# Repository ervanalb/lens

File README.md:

# lens
*lens* stands for "live editing of network streams"

*lens* is a framework that allows you to tap live cabling for inspection and injection.

Defcon 23
=========

Watch the video of our presentation [here](https://www.youtube.com/watch?v=RoOqznZUClI)!

[Slides](docs/LENS_DEFCON_23_slides.pdf) & [whitepaper](docs/lens_whitepaper.pdf) are available in the [docs/](docs) folder.

Or, photos of the device we presented can be found [here](http://eric.van.al/lens).

You can reach us through github, or our emails are listed in our github profiles ([Zach](https://github.com/zbanks/), [Eric](https://github.com/ervanalb/)).

Hardware
========

The wires of a network cable can be punched down into the *lens* tap board in two places without interrupting the packet flow. The tap board then provides a redundant copper path through a set of relays. Once all of the wires have been punched down on both sides, they can be cut so that the signals are now routed only through the relays on the tap board.

One or two additional NICs are connected to the tap board on its TAP ports. These, along with a USB link, are connected to a computer. The computer can command the relays over USB to assume either a passive or active tap topology, or a transparent pass-through mode.

The tap board has three safety features: fail-safe power loss, heartbeat, and tamper detection. If the board detects that power has been lost, it can optionally use the remaining energy stored in a large capacitor to revert the state of the relays to pass-through mode. Alternatively, if the board fails to receive a heartbeat from the computer within a specified amount of time, such as if the computer software crashes, it can revert the relays. Lastly, the board has an accelerometer on it that can detect if the board is jostled or moved and report that to the computer. This can give you peace of mind that your board is still in-place and working.

Software
========

The *lens* software was made to work nicely with the tap board, but can be used without it. Simply connect two NICs in a man-in-the-middle configuration.

*lens* implements a software network stack designed for man-in-the-middle attacks. It is able to decode many protocols, edit their data payloads, and forge new packets containing the modified payloads that look as similar to the original ones as possible.

*lens* is single-threaded and uses asynchronous I/O through *tornado*. Many operations are implemented as tornado coroutines.

Network Layers
--------------

The software is split into *layers*, each of which manages its own state and provides an abstraction for the layers above it. These layers generally follow the standard "OSI Model." For instance, *Ethernet*, *IPv4*, *TCP*, *HTTP*, are some of the layers we have.

### State & Connections

Some layers are inherently stateful with respect to the data that is passed through them (e.g. TCP), whereas others do not require any state to handle their data (e.g. IPv4). However, these layers may find it useful to maintain state in order to later forge packets.

Layers are represented as subclasses of ``NetLayer``. Layers are chained together to form a doubly-linked DAG (typically a tree), where each layer knows its *parent* (``parent``) and its *children* (``children``) that come "above" it in the stack. For example, an instance of ``EthernetLayer`` may have an ``IPv4Layer`` in its ``children`` list. That ``IPv4Layer``'s ``parent`` would be a reference back to the ``EthernetLayer`` instance.

For the purposes of this document, this kind of relationship will be described as ``EthernetLayer --> IPv4Layer``, even though the connection is in fact double-ended, and the layers are instances.

### Methods

Each layer (subclassing ``NetLayer``) should implement the following methods as tornado coroutines:

- ``Layer.on_read(self, src, header, payload)``

This coroutine is called whenever there is new data (``payload``) available for the layer to process. ``header`` is a ``dict`` which holds all of the information extracted from all of the previous layers. With ``payload`` and ``header``, it should be possible to completely reconstruct the original packet. ``src`` represents where the data came from. A simple ``on_read`` might move some data from ``payload`` into ``header`` and call ``Layer.bubble(src, new_header, sub_payload)`` to pass data to children layers.

- ``Layer.write(self, dst, header, payload)``

This coroutine is called to write out ``payload``. A simple ``write`` would take relevant parameters in ``header``, re-serialize them, and combine them with ``payload`` to form a new payload. It would then call ``Layer.write_back(dst, header, new_payload)`` to pass the back to the parent layer.

- ``Layer.match(self, src, header)``

This function should return a boolean indicating whether this layer is capable of handling the given packet. The default behavior, if not overridden, is to always return ``True``, that is, consume all data.

#### Routing

Currently, ``src`` and ``dst`` parameters represent which physical NIC the message came from or is intended to go to. ``NetLayer`` implements two functions, ``route(src)`` and ``unroute(dst)``, which are intended to resolve the intended recipient of a packet. This mechanism might need to be re-worked for systems with 3+ NICs. Currently, the two NICs are represented by ``0`` and ``1``, so the functions are equivalent.

#### Useful Methods

Although each ``NetLayer`` should implement the methods above, there are some additional helper methods/coroutines that are useful:

- ``Layer.bubble(self, src, header, payload)``

This coroutine will attempt to further decode a payload using this layer's ``children``. It will go through the list of children until it finds one whose ``match(...)`` function returns ``True``. It will then call that child's ``on_read(...)`` function. If no child matches, it calls ``self.write(dst, ...)``, resolving ``dst`` from ``src``, at which point the program flow "reverses direction".

This method is used to pass data on to higher layers for further decoding. If no higher layer is available or connected it will re-write (loopback) the data unchanged.

- ``Layer.write_back(self, dst, header, payload)`` 

This coroutine calls ``self.parent.write(dst, header, payload)``. It is for further encoding a payload using this layer's ``parent``. It can be thought of as the opposite of ``Layer.bubble(...)``.

- ``Layer.passthru(self, src, header, payload)``

This convenience coroutine will call ``self.write_back(dst, ...)`` with ``dst`` resolved from ``src``.

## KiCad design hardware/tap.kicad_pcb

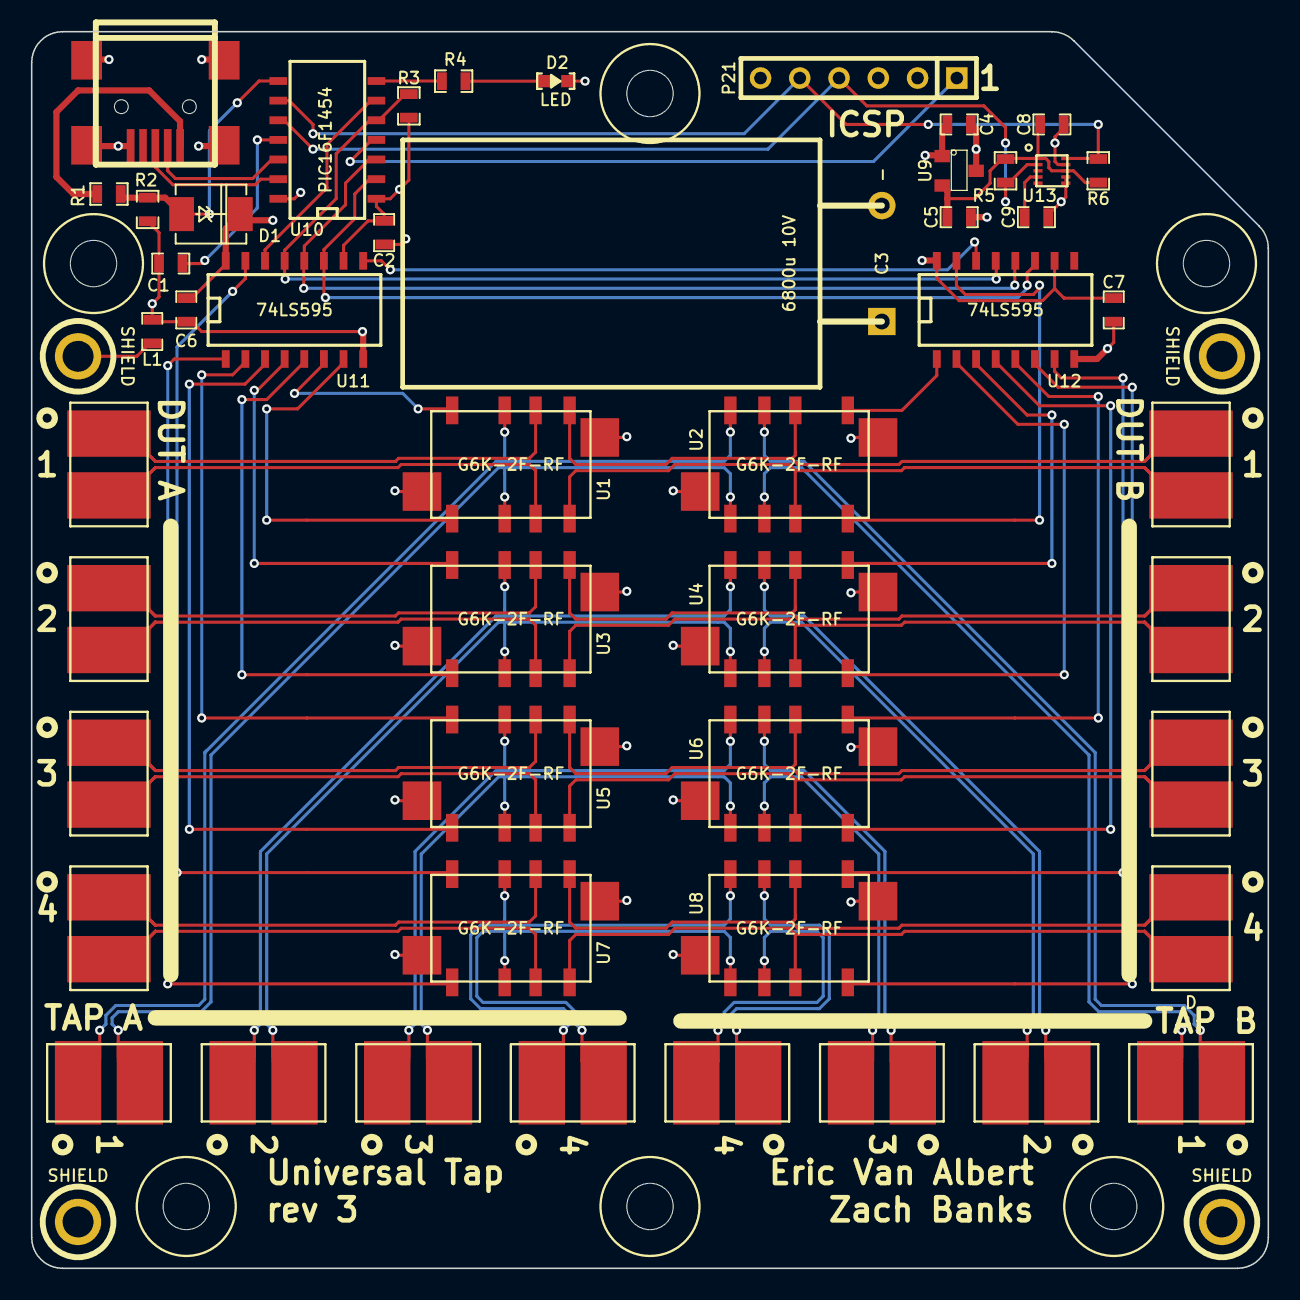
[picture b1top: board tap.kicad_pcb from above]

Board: 4 copper layers, 80.0 x 80.0 mm, 59 parts (0 on the bottom side), 68 nets.

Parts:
C1: 470nF; SM0603_Capa
C2, C6, C7, C8, C9: 100n; SM0603_Capa
C3: 6800u 10V; C2V10
C4, C5: 1u; SM0603_Capa
CON1: USB-MINI-B; USB_MINI_B
D1: DIODE; DO-214AC(SMA)
D2: LED; LED-0603
HOLE: VAL**; HOLE
HOLE#2, HOLE#3, HOLE#4, HOLE#5, HOLE#6: VAL**; HOLE
L1: FERRITE; SM0603_Capa
P1, P6, P11, P16: H; 00-9176-002
P2, P7, P12, P17: HTAP; 00-9176-002
P3, P8, P22, P23: CONN_1; 1pin
P4, P9, P14, P19: DTAP; 00-9176-002
P5, P10, P15, P20: D; 00-9176-002
P21: ICSP; SIL-6
R1: 22R; SM0603_Resistor
R2, R3: 10K; SM0603_Resistor
R4: 100R; SM0603_Resistor
R5, R6: 4K7; SM0603_Resistor
U1, U2, U3, U4, U5, U6, U7, U8: G6K-2F-RF
U9: 3v3; SOT23
U10: PIC16F1454; SO14N
U11, U12: 74LS595; SO16N
U13: MMA8653FC; DFN_10

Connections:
3V3: C5.1, C8.1, R5.1, R6.1, U9.2, U13.1, U13.8
/1/DC+: U2.1, U12.1
/1/DC-: U2.8, U12.15
/1/HC+: U1.1, U11.7
/1/HC-: U1.8, U11.6
/2/DC+: U4.1, U12.3
/2/DC-: U4.8, U12.2
/2/HC+: U3.1, U11.5
/2/HC-: U3.8, U11.4
/3/DC+: U6.1, U12.5
/3/DC-: U6.8, U12.4
/3/HC+: U5.1, U11.3
/3/HC-: U5.8, U11.2
/4/DC+: U8.1, U12.7
/4/DC-: U8.8, U12.6
/4/HC+: U7.1, U11.1
/4/HC-: U7.8, U11.15
/MCLR: P21.1, U10.4
/RCK: U10.3, U11.12, U12.12
/SCK: U10.2, U11.11, U12.11
/SCL: P21.4, R5.2, U10.10, U13.2
/SDA: P21.5, R6.2, U10.9, U13.10
/SER: U10.6, U11.14
/VBUS: D1.1, R1.2, R2.1, U10.8
/~REN: R3.2, U10.5, U11.13, U12.13
AGND: L1.2, P3.1, P8.1, P22.1, P23.1, U1.9, U1.10, U2.9, U2.10, U3.9, U3.10, U4.9, U4.10, U5.9, U5.10, U6.9, U6.10, U7.9, U7.10, U8.9, U8.10
GND: C1.2, C2.1, C3.2, C4.2, C5.2, C6.1, C7.1, C8.2, C9.1, CON1.5, CON1.6, CON1.7, CON1.8, CON1.9, D2.2, L1.1, P21.3, R2.2, U9.1, U10.14, U11.8, U12.8, U13.6, U13.7, U13.9
unnamed: R4.2, U10.7
unnamed: C9.2, U13.4
unnamed: CON1.3, U10.13
unnamed: CON1.2, U10.12
unnamed: CON1.1, R1.1
unnamed: U11.9, U12.14
unnamed: C1.1, U10.11
unnamed: D2.1, R4.1
unnamed: P1.2, U1.3
unnamed: P1.1, U1.6
unnamed: P2.2, U1.2, U2.5
unnamed: P4.1, U2.3
unnamed: P4.2, U2.6
unnamed: P5.1, U1.5, U2.2
unnamed: P5.2, U1.4, U2.7
unnamed: P2.1, U1.7, U2.4
unnamed: P6.1, U3.6
unnamed: P6.2, U3.3
unnamed: P9.2, U4.6
unnamed: P7.2, U3.2, U4.5
unnamed: P9.1, U4.3
unnamed: P10.1, U3.5, U4.2
unnamed: P10.2, U3.4, U4.7
unnamed: P7.1, U3.7, U4.4
unnamed: P11.2, U5.3
unnamed: P11.1, U5.6
unnamed: P12.2, U5.2, U6.5
unnamed: P14.1, U6.3
unnamed: P14.2, U6.6
unnamed: P15.1, U5.5, U6.2
unnamed: P15.2, U5.4, U6.7
unnamed: P12.1, U5.7, U6.4
unnamed: P16.2, U7.3
unnamed: P17.2, U7.2, U8.5
unnamed: P16.1, U7.6
unnamed: P19.1, U8.3
unnamed: P19.2, U8.6
unnamed: P20.1, U7.5, U8.2
unnamed: P20.2, U7.4, U8.7
unnamed: P17.1, U7.7, U8.4
VCC: C2.2, C3.1, C4.1, C6.2, C7.2, D1.2, P21.2, R3.1, U9.3, U10.1, U11.10, U11.16, U12.10, U12.16

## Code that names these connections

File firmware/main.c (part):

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#pragma config FOSC = INTOSC //Intrenal RC oscillator Enabled
#pragma config WDTE = ON    //Watch Dog Timer Disabled.
#pragma config PWRTE= ON     //Power Up Timer Enabled
#pragma config MCLRE = ON    //MCLR pin function Enabled
#pragma config CP = OFF      //Flash Program Memory Code Protection Disabled
#pragma config BOREN = ON    //Brown-out Reset enabled
#pragma config CLKOUTEN = OFF//CLKOUT function is disabled.
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    TRISCbits.TRISC3 = 0;

    LATCbits.LATC4 = 0;
    TRISCbits.TRISC4 = 0; // SER

    LATAbits.LATA4 = 0;
    TRISAbits.TRISA4 = 0; // RCK

    LATAbits.LATA5 = 0;
    TRISAbits.TRISA5 = 0; // SCK
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    zero_sr();

    LATCbits.LATC5 = 0;
    TRISCbits.TRISC5 = 0; // ~REN

    // Enable TMR0 prescaler
    OPTION_REGbits.TMR0CS = 0;
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inline void zero_sr()
{
    uint16_t i;
    LATCbits.LATC4 = 0; // SER = 0
    for(i=0;i<16;i++)
    {
        short_pause();
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        LATAbits.LATA5 = 0; // SCK low
    }
    short_pause();
    LATAbits.LATA4 = 1; // RCK high
    short_pause();
    LATAbits.LATA4 = 0; // RCK low
}

inline void WriteRelays(uint16_t bits)
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        bits >>= 1;
    }
    short_pause();
    LATAbits.LATA4 = 1; // RCK high
    short_pause();
    LATAbits.LATA4 = 0; // RCK low

    latch_pause();

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
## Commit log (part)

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2015-01-21 initial commit of hardware design
2015-01-21 adding basic python utilities
2015-01-21 Turn ethernet into class; standard interface like WSGI
    WSGI uses functions of the form:
    ```
    def app(environ, start_response):
    ...
    ```
    For detour, functions take the form:
2015-01-22 Issues with packet size > 1024
2015-01-22 brian is a fuckup
2015-01-22 improving things
2015-01-22 removing dead code and moving TAP board control into ethernet
2015-01-22 small cleanup
2015-01-22 Python 2 & scapy
2015-01-22 making LED be on when MITM mode is active
2015-01-22 Strip final two bytes from incoming data
2015-01-22 End to end proof of concept
2015-02-05 Starting TCP mitm
2015-02-05 TCP state machine
2015-02-06 cloud to butt sandwich mostly works
2015-02-21 TCP Mimicing and cloud/butt
2015-02-22 Confused about coroutines
2015-02-27 Big commit: re-wrote filters; tornado + coroutines
    Now using tornado-powered coroutines for async
    dpkt instead of scapy, theoretically easier to port to python3
    Filters are now classes (and can have state) which have
    `on_read` and `write` methods.
    Timestamp estimator (which doesn't work well?)
    Basic TCP stack working (3-way handshake & data). Still needs
2015-02-27 Dropped tcp.py by accident (there's a joke here somewhere...)
2015-03-19 Stateful layers; TCP RST, TCP FIN seq half implemented
2015-03-24 TCP WORKS\!
2015-03-24 Restructure NetLayer read/write to have header/data parts
    Now higher levels do not need to understand the lower levels to write
2015-03-24 Cleaning up tcp.py, moving to estimated ts_val's
2015-03-25 Refactored out TCPAppLayer
2015-03-27 steady progress on udp video
2015-03-29 Camera loop & iframes
2015-05-04 Whitepaper
2015-05-05 Final draft of whitepaper
2015-05-25 Working on tests; README
2015-05-25 More HTTP with header adjustments!
2015-05-25 Refactor children/parent; argument order
2015-05-26 PipeLayer for streaming through shell commands
2015-05-26 Cloud-to-butt works again over HTTP
2015-05-27 adding firmware
2015-05-27 add gitignore for mplab and commit a hex file
2015-05-27 adding released board layouts
2015-06-20 Handle both sides of HTTP
2015-06-22 Heartbeat in driver
2015-06-22 Image flipping
2015-06-22 HTTP Keep-alive
2015-06-22 Remove HTTP caching headers; add TCP MSS negotiation
2015-07-10 fixing my shit
2015-07-10 adding .gitignore for hardware
2015-07-10 add some graphics
2015-07-22 Cleanup of python scripts
2015-07-22 Missed test.py
2015-07-22 Adding pyusb to requirements.txt
2015-07-27 Fixing TCPPassthruLayer child resolution
2015-07-27 UDP video logging
2015-07-27 More test scripts
2015-07-28 UDP has been really broken apparently
2015-07-28 Respect TCP MSS from server
2015-07-28 add timestamp preservation ffmpeg example
2015-07-28 Framework for command shell
2015-07-28 Changing nics back
2015-07-28 you are being haxed
2015-07-28 Oops
2015-07-28 Basic shell works
2015-07-28 make default NIC names tapa and tapb and add example udev rule to get this behaviour
2015-07-30 Video manipulation that acutally works?
2015-07-30 Fixed do_loop bug
2015-07-30 remove broken UDP layer, add support for parsing incoming unfragmented NAL packets, fix outputting unfragmented NAL packets
2015-07-30 add non-blocking write, working with my setup now
2015-07-31 Split UDPVideoLayer into H.624 NAL / ffmpeg layers
2015-07-31 Cleaning up NAL code
2015-07-31 Cleaned up ffmpeg layer
2015-07-31 Fixed 'tcp list' command
2015-07-31 TCP/HTTP/c2b/imgflip all work
2015-07-31 change tree structure
2015-07-31 Merged in new match style
2015-07-31 UI looping!
2015-07-31 add / del from UI
2015-07-31 register all layers with UI
2015-07-31 Loop on i-frames
2015-07-31 gracefully switch over to FFMPEG
2015-07-31 gg @zbanks
2015-07-31 have some more fun
2015-07-31 Shell commands for Ethernet & IP
2015-07-31 Trying to merge
2015-07-31 Cleaning up some bad ideas
2015-08-01 Rearch'd shell
2015-08-01 Broke the build, I'm a bad person, etc.
2015-08-01 More robust command finding
2015-08-01 add tamper functionality & script
2015-08-01 Buffering to ffmpeg is hard
2015-08-01 Fixed UI commands
2015-08-01 H264 per-connection
2015-08-01 clean up ffmpeg layer, split out record functionality, make FIFOs nicely
2015-08-01 add recorder layer to sandwich and make tree printing better
2015-08-01 fix errors in recorder
2015-08-01 Reworking UI
2015-08-01 fix del
2015-08-01 rewrite linklayer to be a subclass of netlayer
2015-08-01 Broke shell io loop?
2015-08-01 pre-pull stash
2015-08-01 split out linklayer
2015-08-01 Fixed shell & shifting to log
2015-08-01 fix ioloop bugs and add error handling
2015-08-01 make use of new add_future routine
2015-08-01 Moving more layers to logging framework
2015-08-01 Break out base things into util
2015-08-02 improve shell (no more registering layers)
2015-08-02 del_rejoin
2015-08-02 Cleaned up RTSP, vim mode!
2015-08-02 Small UI help tweaks
2015-08-02 ffmpeg layer arguments
2015-08-02 ctrl-c doesn't quit
2015-08-02 Fixing up HTTP
2015-08-02 More robust HTTP
2015-08-02 move around files for demos
2015-08-02 add demos
2015-08-02 fix paths and make it real again
2015-08-02 bugfixes
2015-08-02 fix demos
2015-08-02 Record wait for IDR
2015-08-03 animation overlay
2015-08-04 Real tap
2015-08-04 Its hard to detect ffmpeg errors
2015-08-04 Adding whitepaper from whitepaper branch
2015-08-05 fix args for ip protos
2015-08-05 Fixing IP/TCP debugging + HTTP uncompressed
2015-08-05 Fixed HTTP re-encoding bug
2015-08-05 Fixed logging/debugging
2015-08-05 fix name and improve replacement in cloud2butt
2015-08-12 Adding slides
2015-08-12 Add notes to README.md re:defcon
2015-08-12 Update README.md
    add link to photos
2015-08-22 clean up repo and libraries, add schematic pdf and BOM
2015-08-22 add photo
2015-08-22 Update README.md
    add photo
2016-06-23 update URL to photos in README
2016-09-02 Starting C port of lens software
2016-09-03 Parsing ethernet & ipv4
2016-09-03 UDP parsing
2016-09-03 Generic packet type; full decode & dump
2016-09-04 More progress on encoding; but not happy with it yet
2016-09-04 Rearranging source in prep for merge
2017-08-09 Revert "Update readme"
    This reverts commit d711bdb8ca7a0040b8eff12b5818a3db6ba18f79.
2018-10-06 readme: Slight rewrite of "Hardware"
    Started with correcting "the provides" to "then provides" and got a bit
    carried away.
